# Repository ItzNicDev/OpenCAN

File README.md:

## 🔍 Project Overview

**OpenCAN** is a microcontroller-based project that reads live OBD-II data (e.g., turbo boost pressure or engine rpm) via Bluetooth and drives an analog pointer using a stepper motor. In a world where dashboards are becoming increasingly digital, **OpenCAN** revives the tactile, satisfying experience of real analog movement—because sometimes, a physical needle sweeping across a dial just feels more alive than pixels on a screen. The goal is to create smooth and responsive pointer movement despite delays in OBD-II data retrieval.

---

## 📑 Table of Contents
1. [🧰 Hardware Components](#-hardware-components)
2. [🏛️ Custom A-pillar trim](#%EF%B8%8F-custom-a-pillar-trim)
3. [🧊 Prepare 3D Printed Parts](#3d-printed-parts)
4. [🪚 Prepare Gauge Enclosure](#-prepare-gauge-enclosure)
5. [⚡️ Custom OpenCAN PCB](#%EF%B8%8F-custom-opencan-pcb)
6. [📟 Use different sensor](#-use-different-sensor)
7. [🔁 Pointer Movement Logic (Interpolation Algorithm)](#-pointer-movement-logic-interpolation-algorithm)
8. [🏃 Code-Flow-Diagram (for boost pressure)](#-code-flow-diagram-for-boost-pressure)
---

## 🧰 Hardware Components

### Core Modules

* 1x [ESP32-DEVKIT-V1](https://de.aliexpress.com/item/1005006128432036.html?spm=a2g0o.productlist.main.1.36c150d9Vynner&algo_pvid=f1c66e43-4416-4eb8-ad0a-b9c25d05ed2b&algo_exp_id=f1c66e43-4416-4eb8-ad0a-b9c25d05ed2b-0&pdp_ext_f=%7B%22order%22%3A%22461%22%2C%22eval%22%3A%221%22%7D&pdp_npi=4%40dis%21EUR%212.14%211.75%21%21%2117.55%2114.36%21%40210385bb17523962162358814e4418%2112000046958263336%21sea%21DE%216233624885%21X&curPageLogUid=PHptQbbetuGY&utparam-url=scene%3Asearch%7Cquery_from%3A) (30-Pin)
* 1x [X27168 Stepper Motor](https://de.aliexpress.com/item/1005001661473145.html?spm=a2g0o.productlist.main.1.5b1e7249E1hdXX&algo_pvid=ca190c73-cd1b-4d43-8954-def95e9eff1c&algo_exp_id=ca190c73-cd1b-4d43-8954-def95e9eff1c-0&pdp_ext_f=%7B%22order%22%3A%227%22%2C%22eval%22%3A%221%22%7D&pdp_npi=4%40dis%21EUR%212.32%211.49%21%21%212.65%211.70%21%402103849717523962718252836e21f9%2112000017032540183%21sea%21DE%216233624885%21X&curPageLogUid=fd8ccaZ4X9Gl&utparam-url=scene%3Asearch%7Cquery_from%3A)
* 1x [ELM327](https://www.amazon.com/-/de/dp/B011NSX27A/ref=sr_1_8?__mk_de_DE=%C3%85M%C3%85%C5%BD%C3%95%C3%91&crid=3SYUDJRW37URA&dib=eyJ2IjoiMSJ9.NUGE1l-88Q6oEUHczfs-yFl6wk7940N2J6GgOT0CBa0Ri1wjB5MQCK3OX5Pm_U1983GKENeZBv8yT7pMUdM9wpxU7IIYhyJWTqZs3SCKHBws1XreI-6Z4mSu40KwRtrpMqGqYzRhD-MW2lm88TroerQCXt3fZSFZbO7ET7Kx0NXpVKG6V2hUOom2woJm2oSBo2X-Kys30ZUsNj2zthKlT3mni4HHp992CAPd4CJpxbqljKjHWIR6I3M2AiaYn96X7NLTGJkHev4e9dZ8e5QSOVbRaNNfRpgY6D1dpdLKGiA.Ekyizh8Yc9gF4pQW3ZJ8Klc2IexRLjBAH_yeWDGDV-0&dib_tag=se&keywords=elm327&qid=1752871228&sprefix=elm327%2Caps%2C180&sr=8-8)

### Power Supply
* 1x [2-Pin Screw Terminal](https://www.amazon.com/-/de/dp/B07QRHJ489?__mk_de_DE=%C3%85M%C3%85%C5%BD%C3%95%C3%91&dib=eyJ2IjoiMSJ9.uJUPY1QHu_fWzphlgpV5C9rjg_-6kPf9AhSlQLb9Lxgu2EzChWYjN7tAZ6Jf-WzKX6FF6YZppyRDppM2nW7oNz7bXXqc-LfImijAoRrFTN8MkNsacd6QBKhOIWn6UlQmwgnNxaHL3NZc-QQOLkMQ-nxxzz4H-Z1QKORLQTGsf65v5CTFbj2D6kPghJDnSBpAYk3Nm0HYQcfwZZjqPUVJ4k--A6OCZ4J9Wg6OBk0eQ10.crXagmvjyYh5XPkeH17DnOu5PxqpbA1QkpEDMX9H0zw&dib_tag=se&keywords=2-Pin%2BScrew%2BTerminal&qid=1752396909&sr=8-3&th=1)
* 1x [CN3903 Buck Converter](https://de.aliexpress.com/item/1005003239596512.html?spm=a2g0o.productlist.main.2.1176599feL7O6y&algo_pvid=c9ccdcb8-a0d6-4b6f-8f0f-f2d4d9f27fd4&algo_exp_id=c9ccdcb8-a0d6-4b6f-8f0f-f2d4d9f27fd4-1&pdp_ext_f=%7B%22order%22%3A%2239%22%2C%22eval%22%3A%221%22%7D&pdp_npi=4%40dis%21EUR%210.45%210.45%21%21%213.67%213.67%21%402103868817523963088208918ec918%2112000024801303076%21sea%21DE%216233624885%21X&curPageLogUid=ReUqz2F9l8rW&utparam-url=scene%3Asearch%7Cquery_from%3A) (12V to 5V)
* 1x [TVS Diode](https://www.amazon.com/dp/B079KHXZHK?psc=1&ref_=cm_sw_r_cp_ud_ct_7PG0FPYTPC88BNJHQAFG_1) (1N6280A)
* 1x [470nF 16V Capacitor](https://de.aliexpress.com/item/1005006075263546.html?spm=a2g0o.productlist.main.23.75b0c9c33Nwfwx&algo_pvid=88c34e0a-e5f4-4e8d-ad2e-4e08d97886e0&algo_exp_id=88c34e0a-e5f4-4e8d-ad2e-4e08d97886e0-20&pdp_ext_f=%7B%22order%22%3A%2214%22%2C%22eval%22%3A%221%22%7D&pdp_npi=4%40dis%21EUR%211.25%211.15%21%21%211.42%211.31%21%40211b6c1917523964976586004e47b6%2112000035613539186%21sea%21DE%216233624885%21X&curPageLogUid=O8hK2Kwejpsj&utparam-url=scene%3Asearch%7Cquery_from%3A)
* 1x [Fuse Holder](https://www.amazon.com/-/de/dp/B074N1NMMX?__mk_de_DE=%C3%85M%C3%85%C5%BD%C3%95%C3%91&crid=2SBTZKT3UCUQ&dib=eyJ2IjoiMSJ9.nHToP20kJLmZshZ_M0ktCMHD9RnAVLlrLyILkyOg4lknW3CdUnjPFvPezVrIsojj-x5a5LbH_jVb_DVyeVXdUkSCjx9jykRxEJOJs6KnH9VgOINRdQscJS-2rSCpN-LD_lS8hbSwVszTsF0Q66Tp0WjJC0yIHGaB9o4uE6svlwgQr0cxuMLgJ_0RaKG_0Viw.0sutghmPgI0P8xBa6hq1SZ7FRD4MUOUzfyrJNIjGa4g&dib_tag=se&keywords=sicherungshalter+pcb&qid=1752396826&sprefix=sicherungshalter+pc%2Caps%2C221&sr=8-30&xpid=1sYgBZV_GLwhn) with [200mA Glass Fuse](https://www.amazon.com/-/de/dp/B074L7Z342?__mk_de_DE=%C3%85M%C3%85%C5%BD%C3%95%C3%91&crid=13Z6DV9I4ZBOU&dib=eyJ2IjoiMSJ9.LIM3b-PhLp5Zu3U4-TNOuEpsv8Xwz1ZNONAtzY1JwJ57WUKEqeybomcOKXZifb_w91XlQu3fEkOsbyxH2hhwrGBx3Tjdw4O55JKQHAp-My_aW8m_vvN66nC-p8kEwng9VIYlZ-A5hHB-413iY5QFCsBTvZoy2Px10v3INejbJEgXiGtwYZWc_V79y10wjGft_u7EylvF7QK2PQ6ovFoYmjSz5XYwrjMQoylsFJFRfkK3eteB7VwcgbsNa3oiJXc_iVU15HVRm8ROSzFozChDlb8WGJkCRdJcjQ-zGeCRoqM.VSXbczhZPxHbQfqDxj-wtgajRLVUzfQy67ioxIvlZ60&dib_tag=se&keywords=glass+fuse+200ma&qid=1752396753&sprefix=glass+fuse+200m%2Caps%2C245&sr=8-5)

### 3D printed Components
* 1x [Gauge Adapter Ring](3D_models/gauge_adapter_ring.3mf)
* 1x [X27168 Adapter Plate](3D_models/x27168_adapter_plate.3mf)
* 1x Gauge Cup

### Additional Components

* 2x [15-Pin Header Socket](https://www.amazon.com/-/de/dp/B08DVGCTKT?__mk_de_DE=%C3%85M%C3%85%C5%BD%C3%95%C3%91&crid=GXC2RSEQUWJJ&dib=eyJ2IjoiMSJ9.F6JUkZTU-stCHqmq-iAIuMEe415-CNFjACNxmpJpwnnrd2NBhMQtE_Y7NULHezwmB6dUmVihC-APueO34gEUiBNyaJpRZ15_bW7hyfXwGCfdxfdZ9eg9GHqSc0hVUuWBBmPzoyE5DJ0V1HI3yE12K4terh7mSPem8wkGEgW4XKGmdQmycc5AUeHSOS2spECj4DL_K3xhjk8wHer8fFmYJRZf6kflPKP6-pJJSFBI0iQ.WnPQ1nI-MXgR_V82nt2K_3ra2xhozqH3QIGRJM6YfT8&dib_tag=se&keywords=pin+header&qid=1752396878&sprefix=pin+header%2Caps%2C221&sr=8-11)
* 3x [M3 Screws](https://de.aliexpress.com/item/1005004527586307.html?spm=a2g0o.productlist.main.7.1c0e83pH83pHDK&algo_pvid=ee12877b-5e38-4728-beaa-28559f366fc3&algo_exp_id=ee12877b-5e38-4728-beaa-28559f366fc3-6&pdp_ext_f=%7B%22order%22%3A%226115%22%2C%22eval%22%3A%221%22%7D&pdp_npi=4%40dis%21EUR%210.96%210.96%21%21%211.09%211.09%21%40210385bb17523969573361899e441d%2112000029486656871%21sea%21DE%216233624885%21X&curPageLogUid=n5f3XXGpyUBB&utparam-url=scene%3Asearch%7Cquery_from%3A)
* 3x [M3 Threaded heat-set inserts](https://de.aliexpress.com/item/1005006472962973.html?spm=a2g0o.productlist.main.1.687c5125OYvhMS&algo_pvid=aa5009d6-1880-4990-88e9-70ea73f17982&algo_exp_id=aa5009d6-1880-4990-88e9-70ea73f17982-0&pdp_ext_f=%7B%22order%22%3A%226242%22%2C%22eval%22%3A%221%22%7D&pdp_npi=4%40dis%21EUR%214.78%211.75%21%21%215.45%211.99%21%40210391a017523970797643092e154c%2112000037324316041%21sea%21DE%216233624885%21X&curPageLogUid=hB6lhYICHs4k&utparam-url=scene%3Asearch%7Cquery_from%3A)
* 1x [Custom OpenCAN PCB](#-pcb-layout) (See [Gerber Files](gerber_files) for further information)
* 1x [Guage Enclosure](https://de.aliexpress.com/item/1005007197636240.html?src=google&pdp_npi=4%40dis!EUR!21.24!10.69!!!!!%40!12000039773227749!ppc!!!&snpsid=1&snps=y&albch=shopping&acnt=272-267-0231&isdl=y&slnk=&plac=&mtctp=&albbt=Google_7_shopping&aff_platform=google&aff_short_key=UneMJZVf&=&albagn=888888&ds_e_adid=&ds_e_matchtype=&ds_e_device=c&ds_e_network=x&ds_e_product_group_id=&ds_e_product_id=de1005007197636240&ds_e_product_merchant_id=5551326180&ds_e_product_country=DE&ds_e_product_language=de&ds_e_product_channel=online&ds_e_product_store_id=&ds_url_v=2&albcp=20536662168&albag=&isSmbAutoCall=false&needSmbHouyi=false&gad_campaignid=19235627944)

---
## 🏛️ Custom a-pillar trim
You may have noticed that the Gauge Cup is only available for the [Suzuki Swift Sport](3D_models/Suzuki_Swift_Sport/Gauge_Cup.3mf). This is because it would be impossible for me as a single person to cover a wide range of vehicles. That's why I only decided to draw such a gauge cup for my car. But in the following I will explain how to make your own gauge cup with simple household tools.

Of course, there are several ways to make a cover for the A-pillar. In the following, however, I will limit myself to the following:

### Molding via wire
Grab a wire that is easy to bend (copper, aluminum) and bend it around the A-pillar at fixed intervals. Stick the pieces of wire onto a sheet of paper with adhesive tape and scan it with a scanner. In the CAD program of your choice, you can arrange and trace the wires scanned by the scanner at the previously fixed distances.

### Molding via 3D-Scan
An app called [Scaniverse](https://scaniverse.com/) is required for this approach. To make it easier for the app to scan or track the A-pillar, it is recommended to apply painter's tape to the surface to be scanned and to apply crosses with a black marker. Export the finished 3D model as an obj file and shape the A-pillar cover in any CAD program using the 3D model as a guide.

⚠️ Important: to ensure that the provided [gauge adapter ring](3D_models/gauge_adapter_ring.3mf) and the [X27168 adapter plate](3D_models/x27168_adapter_plate.3mf) fit, make sure that the hole for the gauge (blue area in the picture below) in the gauge cup has a diameter of 55.15mm or a radius of 27.575mm.

---

## 🧊3D Printed Parts
* 1x [Gauge Cup](3D_models/Suzuki_Swift_Sport/Gauge_Cup.3mf) (you don't own a suzuki swift sport, see "🏛️ Custom A-pillar trim")
* 1x [Gauge Adapter Ring](3D_models/gauge_adapter_ring.3mf)
* 1x [X27168 Adapter Plate](3D_models/x27168_adapter_plate.3mf)

Don’t have a 3D printer? No problem! Services like [JLCPCB](https://jlc3dp.com/3d-printing-quote) now offer 3D printing too – you can upload the models directly and have them printed and shipped to you. Just make sure to choose a heat-resistant material since temperatures inside a car can get pretty high, especially in summer.

---

### 🧊 Prepare 3D Printed Adapter Plate
This part consists of melting the **threaded heat-set inserts** (M2) into the [X27168 adapter plate](3D_models/x27168_adapter_plate.3mf) both top and bottom and mounting the **X27168** step motor with the **M2 screws**.

## 🪚 Prepare Gauge Enclosure
Remove the nuts marked in the picture

---
Cut along the marked line with a dremel to separate the glass part from the rest. Carefully remove the unit from the cut-open enclosure and put it away in the meantime and sand the rough edges of the enclosure. Be careful not to scratch the front of the glass while cutting and sanding. It helps to cover it with masking tape.

---

Take your unit from before and carefully lift the plastic sheet scale at one of the red marked tabs to remove it from the plastic cage completely.

---

Now that the plastic sheet scale has been removed, 2 screws will appear. Unscrew these and you will notice that the circuit board (white), the plastic cage (black plastic with conical top in the middle) and the rear brass part are now separated from each other. The brass part is no longer important for us and has no further use.

---

Now the plastic sheet scale, the plastic cage (black plastic with conical top in the middle) and the pcb (background lighting) can be combined with the previously assembled adapter plate.

---

## ⚡️ Custom OpenCAN PCB
### Schematic

---

### PCB

---

### Ordering
The custom pcb can be ordered from manufacturers such as [JLCPCB](https://cart.jlcpcb.com/quote?spm=Jlcpcb.Homepage.1006). In the case of [JLCPCB](https://cart.jlcpcb.com/quote?spm=Jlcpcb.Homepage.1006), it is recommended to choose the lead-free HASL for the surface finish for health reasons. The PCB color can also be selected, but this may incur additional costs. Also make sure that a PCB thickness of 1.6 mm is selected

---

### ⚡ Electrical Flow Diagram

```text
12V (Car Battery)
├── TVS Diode
├── LED (optional)
├── Buck Converter (12V → 5V)
│   ├── Fuse (200mA)
│   ├── Capacitor (470nF)
│   └── ESP32
│       ├── Buzzer
│       └── Stepper Motor (X27168)
```

---

## 📟 Use different sensor
Of course, it is also possible to read from sensors other than boost pressure or rpm. There is a detailed documentation on [Wikipedia](https://en.wikipedia.org/wiki/OBD-II_PIDs) which lists a number of sensors including PIDs and conversion formulas. OpenCAN is designed so that other sensor types can be added relatively easily. 

To add a new sensor type you must first find the correct PID and the conversion formula. Now you have to define a new [sensor type](platformio_project/include/ObdSensorType.h). Next, the new sensor type must be specified in the [obdSensorHexMap](platformio_project/include/ELM327Driver.h#L20) with [sensor type](platformio_project/include/ObdSensorType.h) and PID. Last but not least, [decodeSensorValue](platformio_project/src/ObdUtils.cpp#L19) must be extended by a case. This contains the handling of the decoding.

---

## 🔁 Pointer Movement Logic (Interpolation Algorithm)

### ⚠️ The Problem

OBD-II data via Bluetooth (e.g., ELM327) introduces blocking delays (typically 80–150 ms). During this blocking time, the microcontroller can't update the motor, resulting in jerky and unresponsive pointer behavior.

### 💡 The Solution: Linear Interpolation

To solve this, OpenCAN simulates smooth transitions between OBD data points using linear interpolation:

#### 1. Periodic, Blocking Data Fetch

* A new target value is fetched every `obdRequestInterval` (e.g., 150ms)
* When new data arrives:

  * Start point (`V0`) is set to the previous target value
  * End point (`V1`) is the newly received value
  * Start time (`t0`) is recorded

#### 2. Continuous Interpolation in Loop

* On every iteration of the `loop()`, if not blocked by data fetch:

  * Calculate progress:

    ```
    progress = (currentTime - t0) / obdRequestInterval
    ```
  * Calculate interpolated target:

    ```
    V_interpolated = V0 + (V1 - V0) * progress
    ```
  * Send `V_interpolated` to `motor.setTargetAngle()`
  * `motor.update()` ensures the motor continuously moves towards this value

### ✅ Result

* The pointer moves smoothly between data points
* Movement appears fluid and responsive, independent of the actual data delay

---

## 🏃 Code-Flow-Diagram (for boost pressure)

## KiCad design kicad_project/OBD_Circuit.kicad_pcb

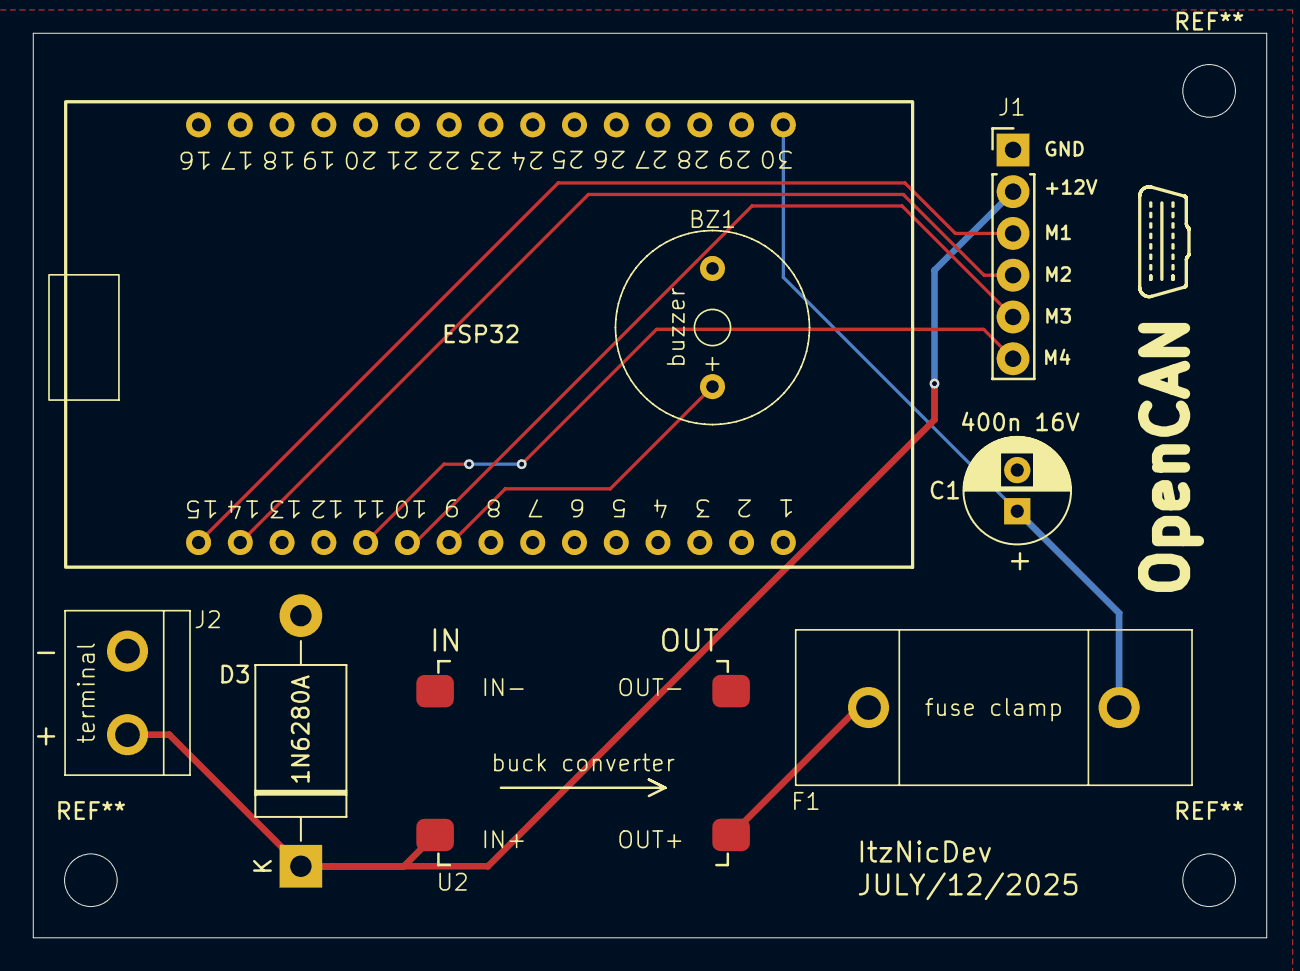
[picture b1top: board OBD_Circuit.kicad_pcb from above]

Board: 4 copper layers, 75.0 x 55.0 mm, 8 parts (0 on the bottom side), 9 nets.

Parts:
BZ1: Buzzer; buzzer
C1: 470n 16V; CP_Radial_D6.3mm_P2.50mm
D3: 1N62xxA; D_DO-201AE_P15.24mm_Horizontal
ESP32: ESP32-DEVKIT-V1; esp32_30pin
F1: 200mA; fuse_clamp
J1: 6Pin; pin_connector_6pin
J2: Screw_Terminal_01x02; screw_terminal_2pin
U2: CN3903 Buck Converter; cn3903_buck_converter

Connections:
+5V: C1.1, ESP32.30 (VIN), F1.2
+12V: D3.1 (A1), J1.2, J2.1, U2.1 (IN+)
GND: BZ1.2 (-), C1.2, D3.2 (A2), ESP32.2 (GND), ESP32.29 (GND), J1.1, J2.2, U2.2 (IN-), U2.4 (OUT-)
unnamed: BZ1.1 (+), ESP32.9 (D18)
unnamed: ESP32.15 (D23), J1.3
unnamed: ESP32.14 (D22), J1.4
unnamed: ESP32.10 (D19), J1.5
unnamed: ESP32.11 (D21), J1.6
unnamed: F1.1, U2.3 (OUT+)

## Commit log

2025-05-10 Rename main.cpp to obd_connect.cpp
2025-05-11 project added
2025-05-11 project created + first helper classes
2025-05-11 .DS_Store added to gitignore
2025-05-11 Remove .DS_Store from tracking
2025-05-11 Remove .vscode from tracking
2025-05-11 Added all helper and utils classes for obd communication
2025-05-16 bugfix/reference method
2025-05-19 feature - added test function for motor
2025-05-28 setTargetAngle added
2025-05-28 setTargetAngle programmed
2025-05-28 removed necessary parts from main
2025-07-13 adjusted file structure
2025-07-13 renamed code folder and added folders for future files
2025-07-13 added gerber files
2025-07-13 kicad files added
2025-07-13 added 3d model and ziped gerber files
2025-07-13 Rename 3D_models/Suzuki_Swift_Sport/gauge_adapter_ring.3mf to 3D_models/gauge_adapter_ring.3mf
2025-07-13 Rename 3D_models/Suzuki_Swift_Sport/x27168_adapter_plate.3mf to 3D_models/x27168_adapter_plate.3mf
2025-07-13 Rename remove_nut_guid.png to remove_nuts_guid.png
2025-07-18 outsourced str_rm_ws into StringUtils + outsourced OBD-response-processing into decodeSensorValue (ObdUtils)
